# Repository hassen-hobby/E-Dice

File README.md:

# E-Dice
PIC 10F322マイコンを使った電子サイコロ<br>
ボタンを押すと7つのLEDがサイコロの目状に変化して止まります。<br>
抵抗とコンデンサは表面実装部品（1608サイズ）<br>
PICはDIPかSOT23-6のどちらか選んで取付けられます。<br>
zipファイルは回路図と基板データ

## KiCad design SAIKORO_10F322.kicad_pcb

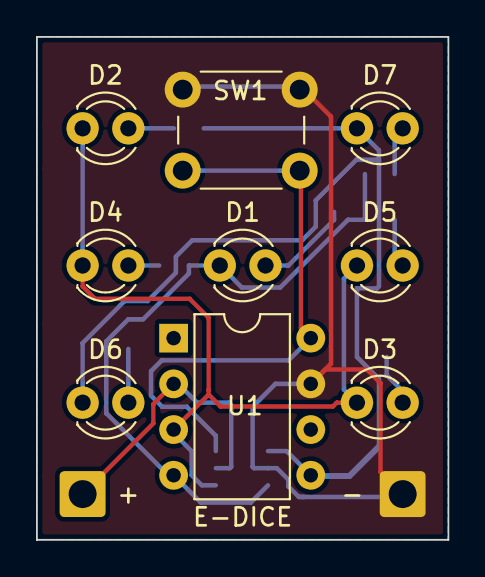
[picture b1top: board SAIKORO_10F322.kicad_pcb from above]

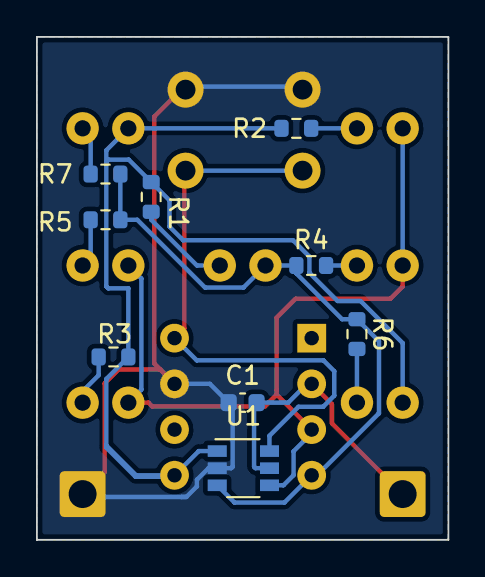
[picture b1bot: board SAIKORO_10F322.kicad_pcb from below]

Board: 2 copper layers, 22.9 x 27.9 mm, 20 parts (9 on the bottom side), 13 nets.

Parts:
+: Conn_01x01; SolderWire-0.75sqmm_1x01_D1.25mm_OD2.3mm
-: Conn_01x01; SolderWire-0.75sqmm_1x01_D1.25mm_OD2.3mm
C1: C; C_0603_1608Metric
D1, D2, D3, D4, D5, D6, D7: LED; LED_D3.0mm
R1, R2, R3, R4, R5, R6, R7: R; R_0603_1608Metric
SW1: SW_Push; SW_PUSH_6mm
U1: PIC10F322-IOT; SOT-23-6
U1#2: PIC10F322-IP; DIP-8_W7.62mm

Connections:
/RA0: D6.1, D7.1, R1.1, R2.1, R3.1, U1.1, U1#2.5
/RA1: D1.1, R4.1, R5.1, R6.1, R7.1, U1.3, U1#2.4
/RA2: D2.1, D3.1, D4.1, D5.1, U1.4, U1#2.3
/SW: SW1.1, U1.6, U1#2.8
GND: -.1, C1.2, SW1.2, U1.2, U1#2.7
unnamed: D1.2, R1.2
unnamed: D2.2, R2.2
unnamed: D3.2, R3.2
unnamed: D4.2, R4.2
unnamed: D5.2, R5.2
unnamed: D6.2, R6.2
unnamed: D7.2, R7.2
VCC: +.1, C1.1, U1.5, U1#2.2
